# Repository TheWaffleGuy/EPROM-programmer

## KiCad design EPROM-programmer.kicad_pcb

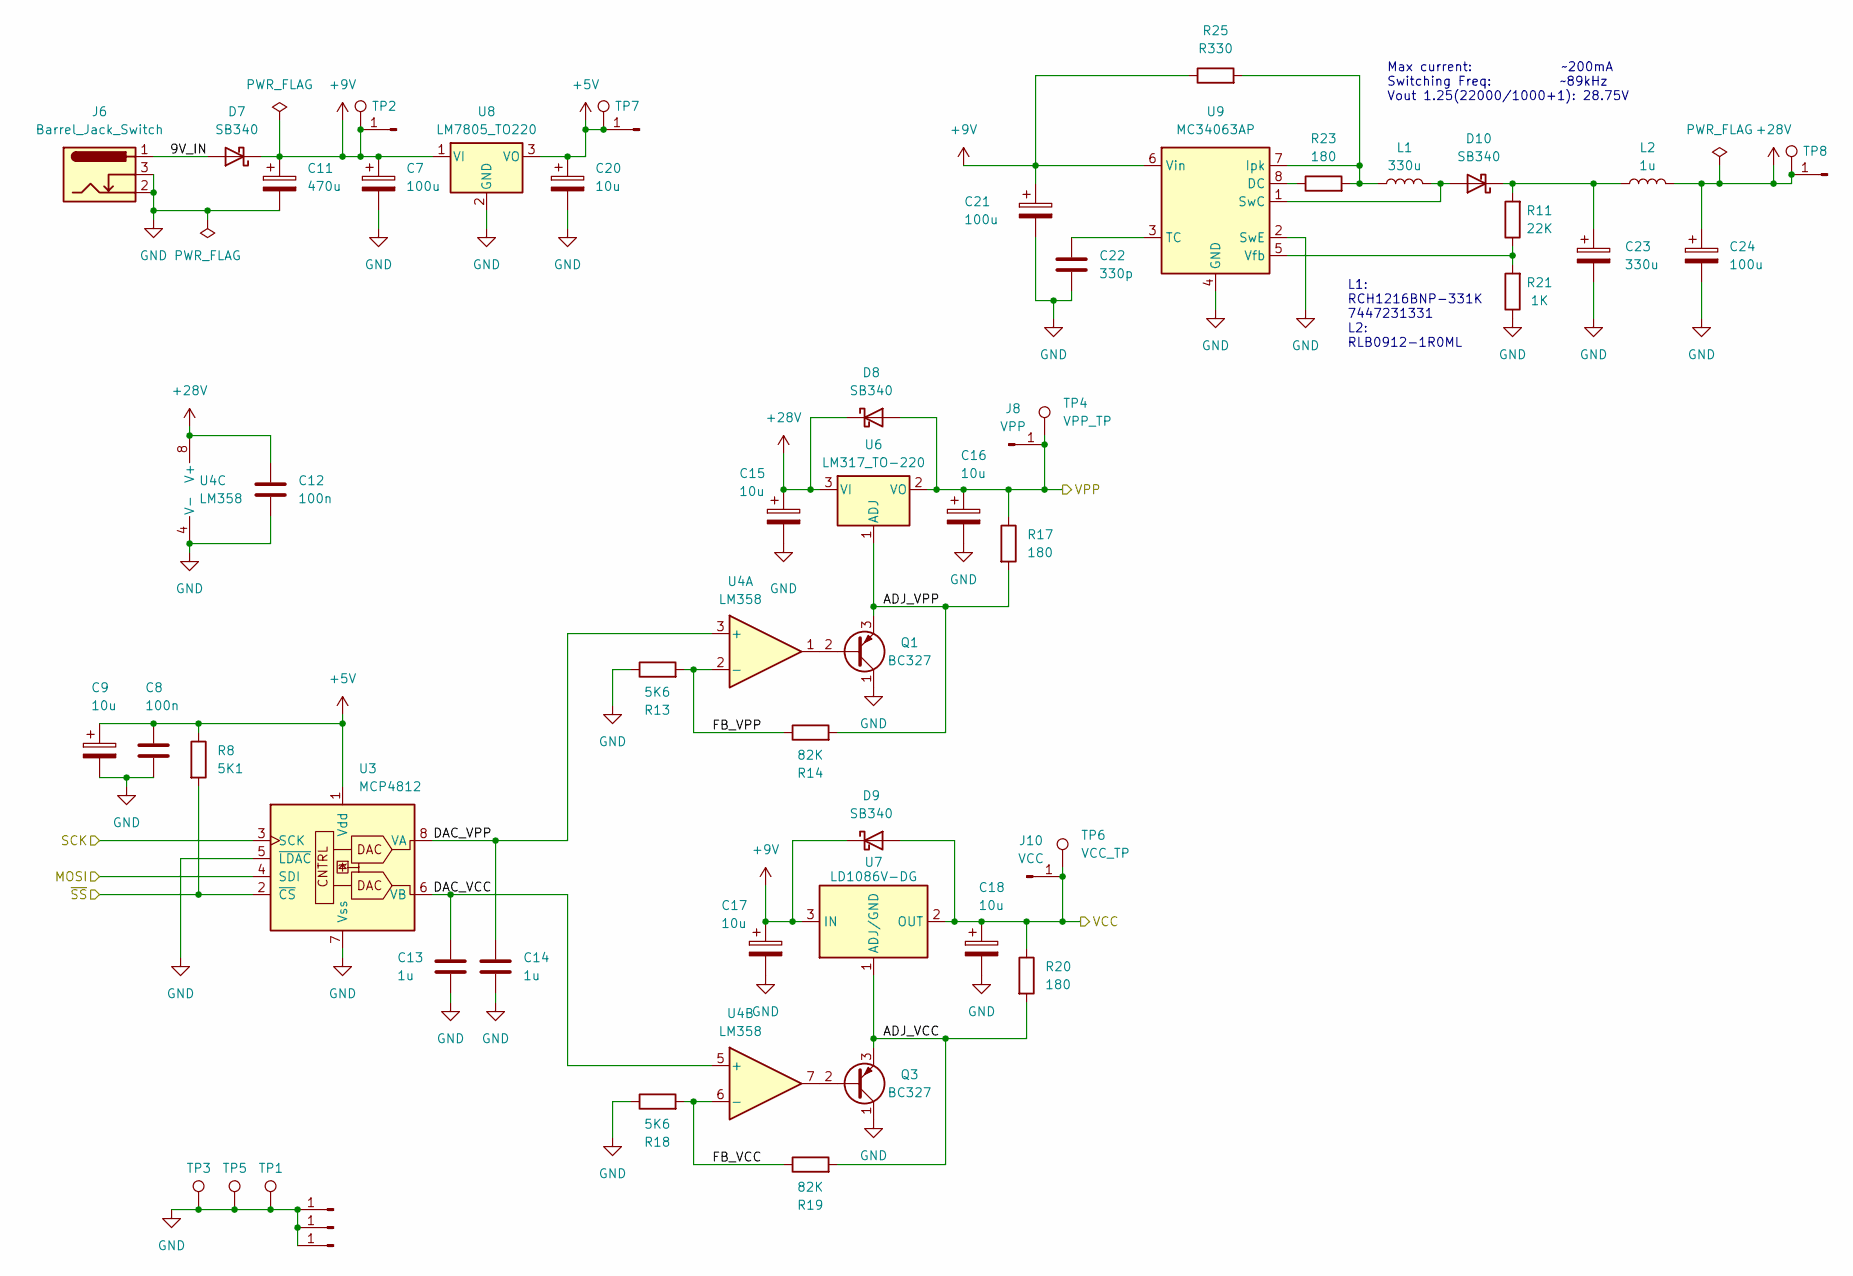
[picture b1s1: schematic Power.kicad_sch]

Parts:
C7, C21, C24: 100u; CP_Radial_D6.3mm_P2.50mm
C8, C12: 100n; C_Rect_L4.6mm_W3.0mm_P2.50mm_MKS02_FKP02
C9, C15, C16, C17, C18: 10u; C_Rect_L4.6mm_W3.0mm_P2.50mm_MKS02_FKP02
C11: 470u; CP_Radial_D10.0mm_P5.00mm
C13, C14: 1u; C_Rect_L4.6mm_W3.0mm_P2.50mm_MKS02_FKP02
C20: 10u; CP_Radial_D6.3mm_P2.50mm
C22: 330p; C_Rect_L4.6mm_W3.0mm_P2.50mm_MKS02_FKP02
C23: 330u; CP_Radial_D10.0mm_P5.00mm
D7, D8, D9, D10: SB340; D_DO-201AD_P5.08mm_Vertical_KathodeUp
J3, J5, J9: GND; PinHeader_1x01_P2.54mm_Vertical
J4: 9V; PinHeader_1x01_P2.54mm_Vertical
J6: Barrel_Jack_Switch; BarrelJack_Horizontal
J8: VPP; PinHeader_1x01_P2.54mm_Vertical
J10: VCC; PinHeader_1x01_P2.54mm_Vertical
J11: 5V; PinHeader_1x01_P2.54mm_Vertical
J12: 28V; PinHeader_1x01_P2.54mm_Vertical
L1: 330u; L_Radial_D12.5mm_P4.00mm_5.00mm
L2: 1u; L_Radial_D8.7mm_P5.00mm_Fastron_07HCP
Q1, Q3: BC327; TO-92_Inline_Wide
R8: 5K1; R_Axial_DIN0207_L6.3mm_D2.5mm_P10.16mm_Horizontal
R11: 22K; R_Axial_DIN0207_L6.3mm_D2.5mm_P10.16mm_Horizontal
R13, R18: 5K6; R_Axial_DIN0207_L6.3mm_D2.5mm_P10.16mm_Horizontal
R14, R19: 82K; R_Axial_DIN0207_L6.3mm_D2.5mm_P10.16mm_Horizontal
R17, R20, R23: 180; R_Axial_DIN0207_L6.3mm_D2.5mm_P10.16mm_Horizontal
R21: 1K; R_Axial_DIN0207_L6.3mm_D2.5mm_P10.16mm_Horizontal
R25: R330; R_Axial_DIN0207_L6.3mm_D2.5mm_P10.16mm_Horizontal
TP1, TP3, TP5: GND; TestPoint_Pad_2.0x2.0mm
TP2: 12V; TestPoint_Pad_2.0x2.0mm
TP4: VPP_TP; TestPoint_Pad_2.0x2.0mm
TP6: VCC_TP; TestPoint_Pad_2.0x2.0mm
TP7: 5V; TestPoint_Pad_2.0x2.0mm
TP8: 28V; TestPoint_Pad_2.0x2.0mm
U3: MCP4812; DIP-8_W7.62mm_Socket
U4: LM358; DIP-8_W7.62mm_Socket
U6: LM317_TO-220; TO-220-3_Vertical
U7: LD1086V-DG; TO-220-3_Horizontal_TabDown
U8: LM7805_TO220; TO-220-3_Horizontal_TabDown
U9: MC34063AP; DIP-8_W7.62mm

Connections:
+5V: C8.1, C9.1, C20.1, J11.1, R8.1, TP7.1, U3.1 (Vdd), U8.3 (VO); also elsewhere on the board
+9V: C7.1, C11.1, C17.1, C21.1, D7.1 (K), D9.1 (K), J4.1, R25.1, TP2.1, U7.3 (IN), U8.1 (VI), U9.6 (Vin)
+28V: C12.1, C15.1, C24.1, D8.1 (K), J12.1, L2.2, TP8.1, U4.8 (V+), U6.3 (VI)
/Power/9V_IN: D7.2 (A), J6.1
/Power/ADJ_VCC: Q3.3 (E), R19.2, R20.2, U7.1 (ADJ/GND)
/Power/ADJ_VPP: Q1.3 (E), R14.2, R17.2, U6.1 (ADJ)
/Power/DAC_VCC: C13.1, U3.6 (VB), U4.5 (+)
/Power/DAC_VPP: C14.1, U3.8 (VA), U4.3 (+)
/Power/FB_VCC: R18.2, R19.1, U4.6 (-)
/Power/FB_VPP: R13.2, R14.1, U4.2 (-)
/Power/VCC: C18.1, D9.2 (A), J10.1, R20.1, TP6.1, U7.2 (OUT); also elsewhere on the board
/Power/VPP: C16.1, D8.2 (A), J8.1, R17.1, TP4.1, U6.2 (VO); also elsewhere on the board
/Power/~SS: R8.2, U3.2 (~CS); also elsewhere on the board
/Programmer/MOSI: U3.4 (SDI); also elsewhere on the board
/Programmer/SCK: U3.3 (SCK); also elsewhere on the board
GND: C7.2, C8.2, C9.2, C11.2, C12.2, C13.2, C14.2, C15.2, C16.2, C17.2, C18.2, C20.2, C21.2, C22.2, C23.2, C24.2, J3.1, J5.1, J6.2, J6.3, J9.1, Q1.1 (C), Q3.1 (C), R13.1, R18.1, R21.1, TP1.1, TP3.1, TP5.1, U3.5 (~LDAC), U3.7 (Vss), U4.4 (V-), U8.2 (GND), U9.2 (SwE), U9.4 (GND); also elsewhere on the board
unnamed: D10.2 (A), L1.2, U9.1 (SwC)
unnamed: C23.1, D10.1 (K), L2.1, R11.2
unnamed: Q1.2 (B), U4.1
unnamed: Q3.2 (B), U4.7
unnamed: R23.1, U9.8 (DC)
unnamed: L1.1, R23.2, R25.2, U9.7 (Ipk)
unnamed: C22.1, U9.3 (TC)
unnamed: R11.1, R21.2, U9.5 (Vfb)

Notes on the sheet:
L1: RCH1216BNP-331K 7447231331 L2: RLB0912-1R0ML
Max current: ~200mA Switching Freq: ~89kHz Vout 1.25(22000/1000+1): 28.75V

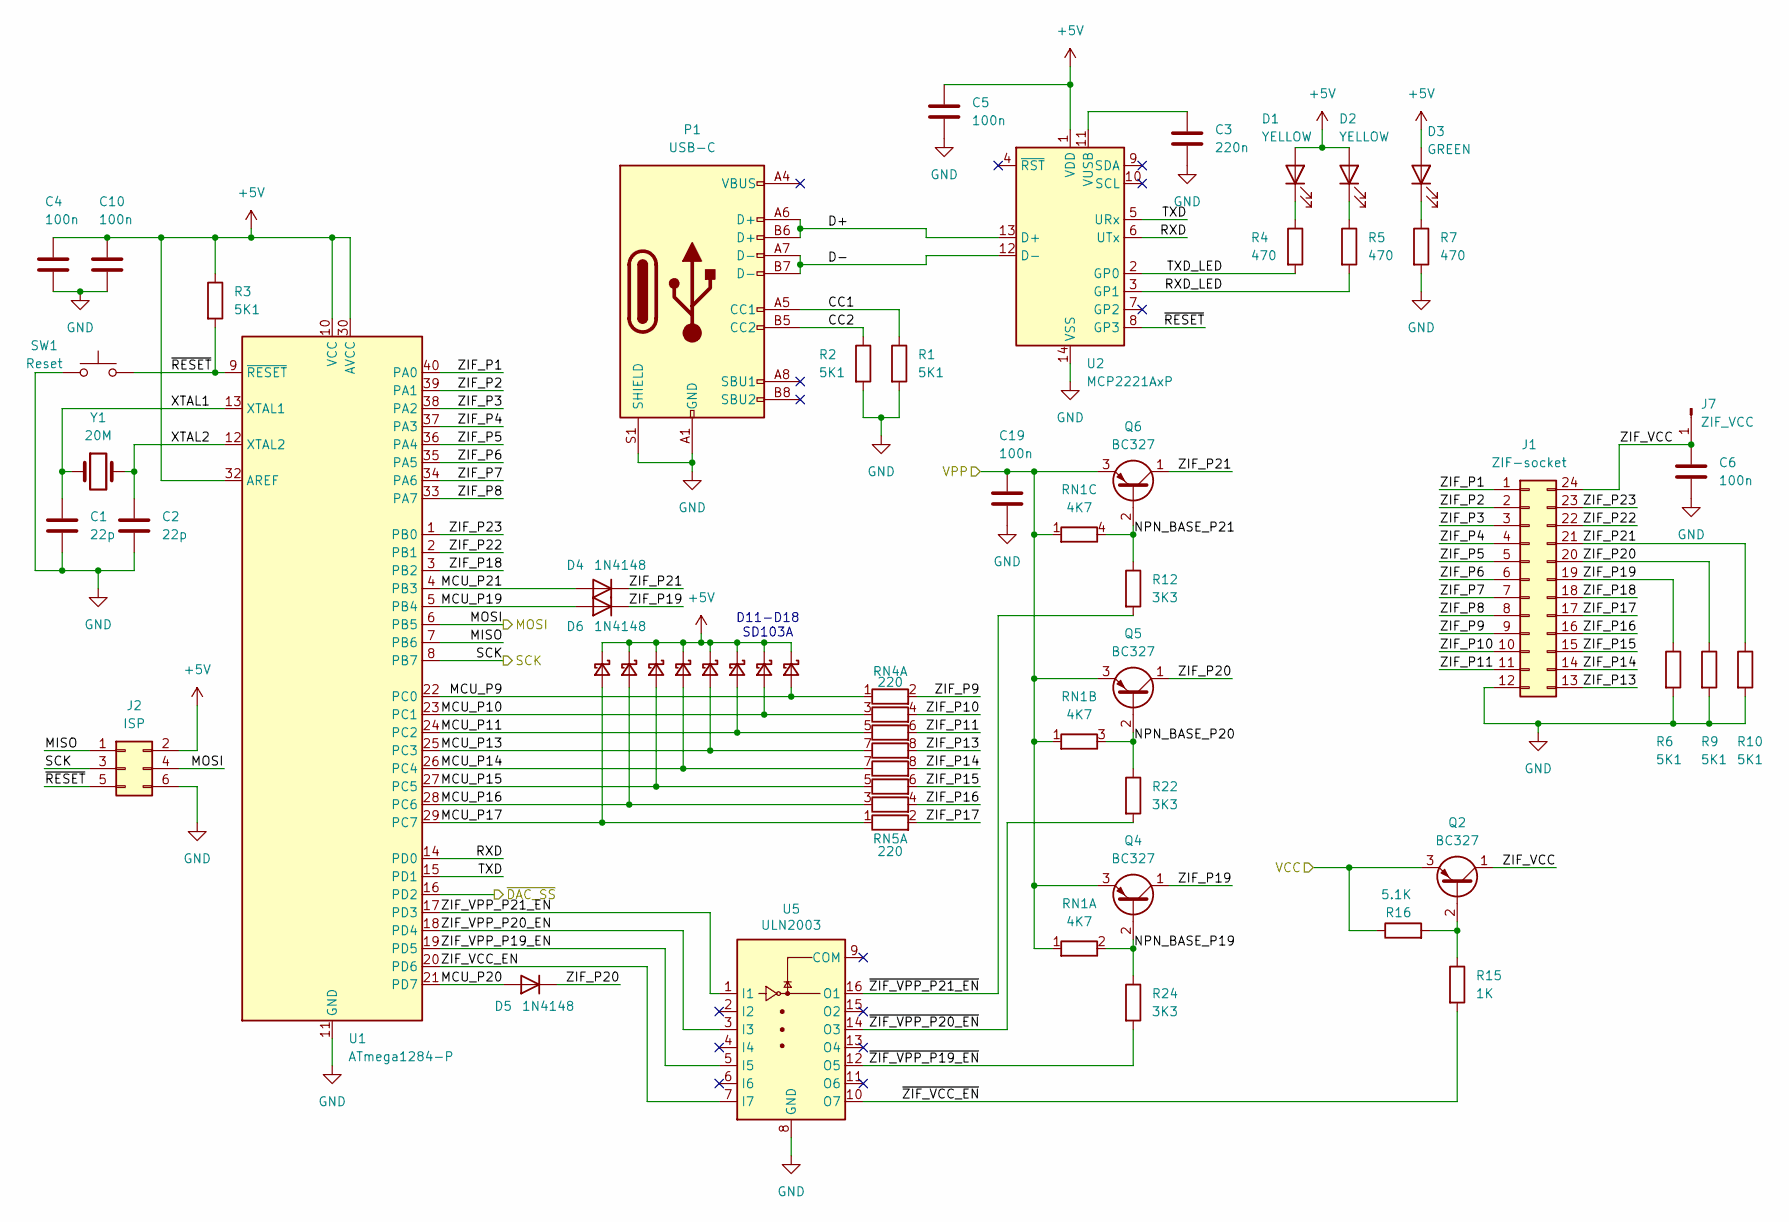
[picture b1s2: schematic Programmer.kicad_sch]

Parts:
C1, C2: 22p; C_Rect_L4.6mm_W3.0mm_P2.50mm_MKS02_FKP02
C3: 220n; C_Rect_L4.6mm_W3.0mm_P2.50mm_MKS02_FKP02
C4, C5, C6, C10, C19: 100n; C_Rect_L4.6mm_W3.0mm_P2.50mm_MKS02_FKP02
D1, D2: YELLOW; LED_D3.0mm
D3: GREEN; LED_D3.0mm
D4, D5, D6: 1N4148; D_DO-35_SOD27_P7.62mm_Horizontal
D11, D12, D13, D14, D15, D16, D17, D18: SD103A; D_DO-35_SOD27_P7.62mm_Horizontal
J1: ZIF-socket; DIP_Socket-24_W11.9_W12.7_W15.24_W17.78_W18.5_3M_224-1275-0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
J2: ISP; IDC-Header_2x03_P2.54mm_Vertical
J7: ZIF_VCC; PinHeader_1x01_P2.54mm_Vertical
P1: USB-C; USB_C_Receptacle_GCT_USB4085
Q2, Q4, Q5, Q6: BC327; TO-92_Inline_Wide
R1, R2, R3, R6, R9, R10: 5K1; R_Axial_DIN0207_L6.3mm_D2.5mm_P10.16mm_Horizontal
R4, R5, R7: 470; R_Axial_DIN0207_L6.3mm_D2.5mm_P10.16mm_Horizontal
R12, R22, R24: 3K3; R_Axial_DIN0207_L6.3mm_D2.5mm_P10.16mm_Horizontal
R15: 1K; R_Axial_DIN0207_L6.3mm_D2.5mm_P10.16mm_Horizontal
R16: 5.1K; R_Axial_DIN0207_L6.3mm_D2.5mm_P10.16mm_Horizontal
RN1: 4K7; R_Array_SIP4
RN4, RN5: 220; R_Array_SIP8
SW1: Reset; SW_PUSH_6mm
U1: ATmega1284-P; DIP-40_W15.24mm_Socket
U2: MCP2221AxP; DIP-14_W7.62mm_Socket
U5: ULN2003; DIP-16_W7.62mm
Y1: 20M; Crystal_HC49-U_Vertical

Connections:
+5V: C4.1, C5.1, C10.1, D1.2 (A), D2.2 (A), D3.2 (A), D11.1 (K), D12.1 (K), D13.1 (K), D14.1 (K), D15.1 (K), D16.1 (K), D17.1 (K), D18.1 (K), J2.2, R3.1, U1.10 (VCC), U1.30 (AVCC), U1.32 (AREF), U2.1 (VDD); also elsewhere on the board
/Power/VCC: Q2.3 (E), R16.1; also elsewhere on the board
/Power/VPP: C19.1, Q4.3 (E), Q5.3 (E), Q6.3 (E), RN1.1 (R1); also elsewhere on the board
/Power/~SS: U1.16 (PD2); also elsewhere on the board
/Programmer/CC1: P1.A5 (CC1), R1.1
/Programmer/CC2: P1.B5 (CC2), R2.1
/Programmer/D+: P1.A6 (D+), P1.B6 (D+), U2.13 (D+)
/Programmer/D-: P1.A7 (D-), P1.B7 (D-), U2.12 (D-)
/Programmer/MCU_P9: D18.2 (A), RN4.1 (R1.1), U1.22 (PC0)
/Programmer/MCU_P10: D17.2 (A), RN4.3 (R2.1), U1.23 (PC1)
/Programmer/MCU_P11: D16.2 (A), RN4.5 (R3.1), U1.24 (PC2)
/Programmer/MCU_P13: D15.2 (A), RN4.7 (R4.1), U1.25 (PC3)
/Programmer/MCU_P14: D14.2 (A), RN5.7 (R4.1), U1.26 (PC4)
/Programmer/MCU_P15: D13.2 (A), RN5.5 (R3.1), U1.27 (PC5)
/Programmer/MCU_P16: D12.2 (A), RN5.3 (R2.1), U1.28 (PC6)
/Programmer/MCU_P17: D11.2 (A), RN5.1 (R1.1), U1.29 (PC7)
/Programmer/MCU_P19: D6.2 (A), U1.5 (PB4)
/Programmer/MCU_P20: D5.2 (A), U1.21 (PD7)
/Programmer/MCU_P21: D4.2 (A), U1.4 (PB3)
/Programmer/MISO: J2.1, U1.7 (PB6)
/Programmer/MOSI: J2.4, U1.6 (PB5); also elsewhere on the board
/Programmer/NPN_BASE_P19: Q4.2 (B), R24.1, RN1.2 (R1.2)
/Programmer/NPN_BASE_P20: Q5.2 (B), R22.1, RN1.3 (R2.2)
/Programmer/NPN_BASE_P21: Q6.2 (B), R12.1, RN1.4 (R3.2)
/Programmer/RXD: U1.14 (PD0), U2.6 (UTx)
/Programmer/RXD_LED: R5.2, U2.3 (GP1)
/Programmer/SCK: J2.3, U1.8 (PB7); also elsewhere on the board
/Programmer/TXD: U1.15 (PD1), U2.5 (URx)
/Programmer/TXD_LED: R4.2, U2.2 (GP0)
/Programmer/XTAL1: C1.1, U1.13 (XTAL1), Y1.1
/Programmer/XTAL2: C2.1, U1.12 (XTAL2), Y1.2
/Programmer/ZIF_P1: J1.1, U1.40 (PA0)
/Programmer/ZIF_P2: J1.2, U1.39 (PA1)
/Programmer/ZIF_P3: J1.3, U1.38 (PA2)
/Programmer/ZIF_P4: J1.4, U1.37 (PA3)
/Programmer/ZIF_P5: J1.5, U1.36 (PA4)
/Programmer/ZIF_P6: J1.6, U1.35 (PA5)
/Programmer/ZIF_P7: J1.7, U1.34 (PA6)
/Programmer/ZIF_P8: J1.8, U1.33 (PA7)
/Programmer/ZIF_P9: J1.9, RN4.2 (R1.2)
/Programmer/ZIF_P10: J1.10, RN4.4 (R2.2)
/Programmer/ZIF_P11: J1.11, RN4.6 (R3.2)
/Programmer/ZIF_P13: J1.13, RN4.8 (R4.2)
/Programmer/ZIF_P14: J1.14, RN5.8 (R4.2)
/Programmer/ZIF_P15: J1.15, RN5.6 (R3.2)
/Programmer/ZIF_P16: J1.16, RN5.4 (R2.2)
/Programmer/ZIF_P17: J1.17, RN5.2 (R1.2)
/Programmer/ZIF_P18: J1.18, U1.3 (PB2)
/Programmer/ZIF_P19: D6.1 (K), J1.19, Q4.1 (C), R6.1
/Programmer/ZIF_P20: D5.1 (K), J1.20, Q5.1 (C), R9.1
/Programmer/ZIF_P21: D4.1 (K), J1.21, Q6.1 (C), R10.1
/Programmer/ZIF_P22: J1.22, U1.2 (PB1)
/Programmer/ZIF_P23: J1.23, U1.1 (PB0)
/Programmer/ZIF_VCC: C6.1, J1.24, J7.1, Q2.1 (C)
/Programmer/ZIF_VCC_EN: U1.20 (PD6), U5.7 (I7)
/Programmer/ZIF_VPP_P19_EN: U1.19 (PD5), U5.5 (I5)
/Programmer/ZIF_VPP_P20_EN: U1.18 (PD4), U5.3 (I3)
/Programmer/ZIF_VPP_P21_EN: U1.17 (PD3), U5.1 (I1)
/Programmer/~RESET: J2.5, R3.2, SW1.2, U1.9 (~RESET), U2.8 (GP3)
/Programmer/~ZIF_VCC_EN: R15.2, U5.10 (O7)
/Programmer/~ZIF_VPP_P19_EN: R24.2, U5.12 (O5)
/Programmer/~ZIF_VPP_P20_EN: R22.2, U5.14 (O3)
/Programmer/~ZIF_VPP_P21_EN: R12.2, U5.16 (O1)
GND: C1.2, C2.2, C3.2, C4.2, C5.2, C6.2, C10.2, C19.2, J1.12, J2.6, P1.A1 (GND), P1.A12 (GND), P1.B1 (GND), P1.B12 (GND), P1.S1 (SHIELD), R1.2, R2.2, R6.2, R7.2, R9.2, R10.2, SW1.1, U1.11 (GND), U1.31 (GND), U2.14 (VSS), U5.8 (GND); also elsewhere on the board
unnamed: D1.1 (K), R4.1
unnamed: D2.1 (K), R5.1
unnamed: D3.1 (K), R7.1
unnamed: Q2.2 (B), R15.1, R16.2
unnamed: C3.1, U2.11 (VUSB)

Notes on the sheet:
D11-D18 SD103A

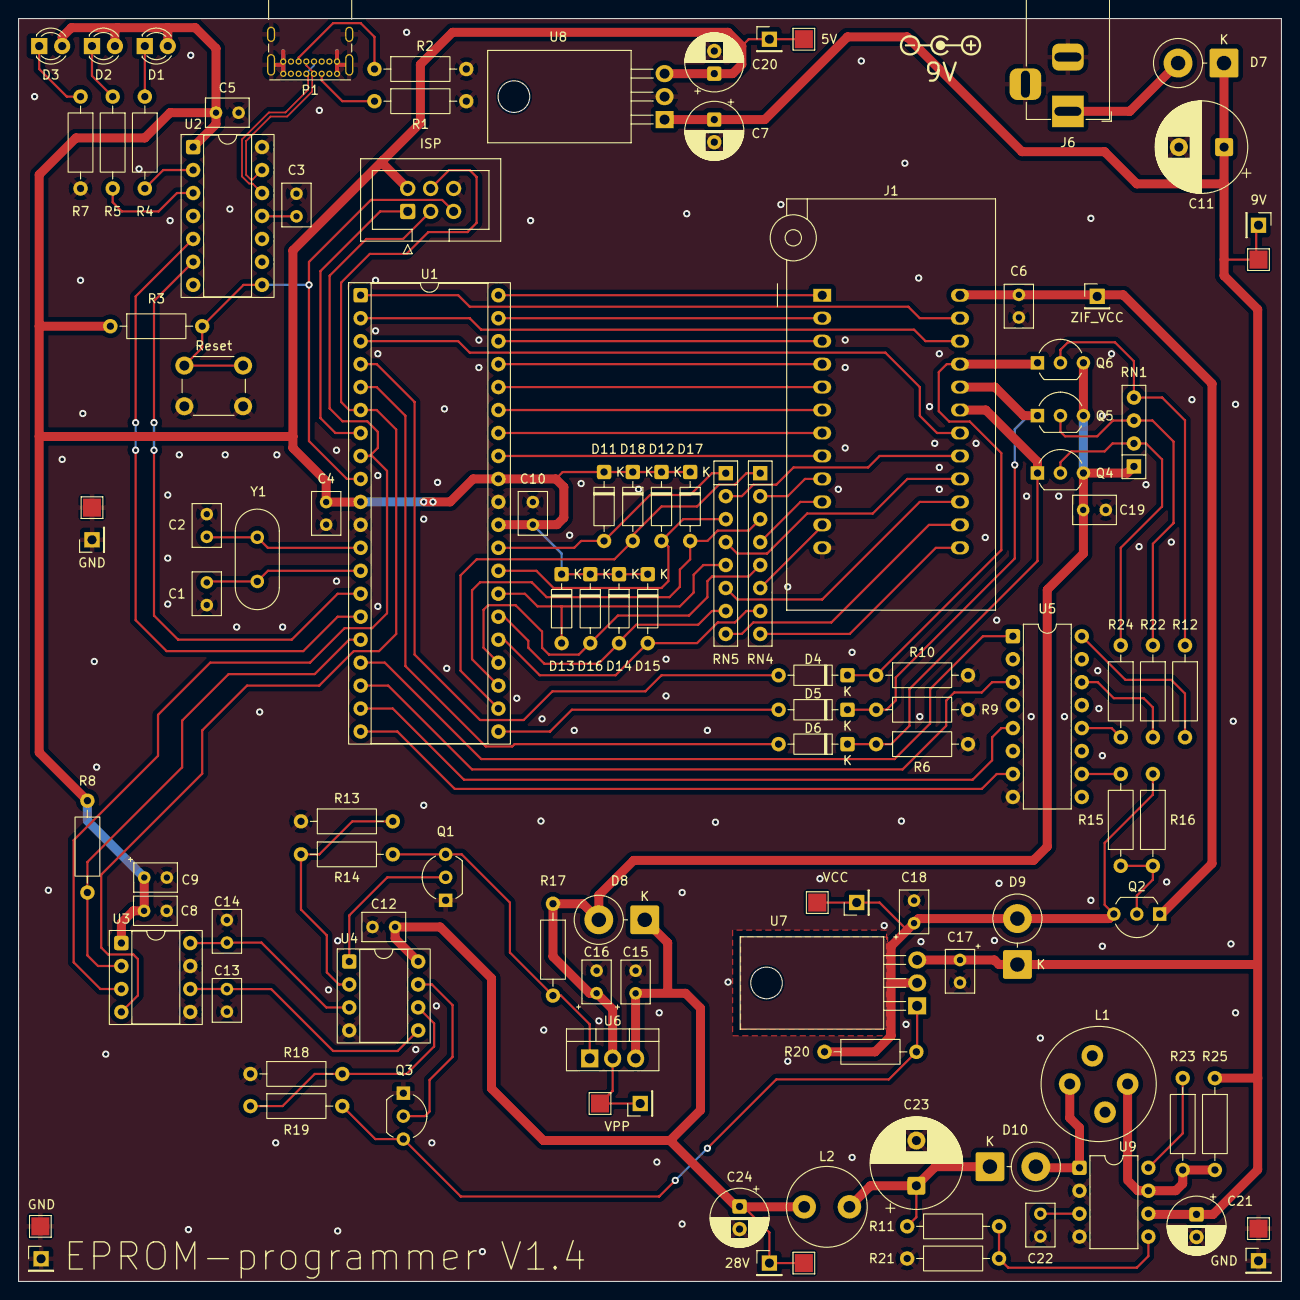
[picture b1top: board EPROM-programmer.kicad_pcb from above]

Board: 2 copper layers, 139.7 x 139.7 mm, 110 parts (0 on the bottom side), 86 nets.

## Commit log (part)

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2023-07-21 Some initial stuff
2023-07-21 Add some LEDs
2023-07-21 Add TODO
2023-07-21 Wire-up ISP, ZIF and more
2023-07-21 Add datasheets
2023-07-22 Add missing foot-prints
2023-07-22 Add power-flags
2023-07-22 Clean-up
2023-07-23 Add DAC and more
2023-07-24 Add datasheet for DAC
2023-07-24 Add some net-labels
2023-07-24 Add missing footprint
2023-07-24 Change to socket footprints
2023-07-24 Very rough component placement
2023-07-24 Add pull-up for select-line for DAC
2023-07-24 Begin routing
2023-07-24 Add more routing
2023-07-25 Update connections to ZIF-socket
2023-07-25 Add test-program
2023-07-25 Add method for writing buffer as srec
2023-07-25 Minor changes
2023-07-25 Add 57C43
2023-07-25 Update 3D-models to populated sockets
2023-07-26 Add model for ZIF-socket
2023-07-26 Minor adjustments
2023-07-26 Fix some DRC errors
2023-07-26 Initial version submitted for manufacturing
2023-07-26 Fix capacitor-stuff
2023-07-27 Begin design power
2023-07-28 Begin working on firmware
2023-07-28 Fix input/output modes of pins
2023-07-28 Send adress-data to ports
2023-07-28 Implement blank-check
2023-07-28 Fix typo
2023-07-28 Implement compare-function
2023-07-28 Print help-text when an unknown command is issued
2023-07-28 Ignore empty commands
2023-07-28 Some refactoring
2023-07-28 Refactor
2023-07-29 Add missing return statements
2023-07-29 Stupid attempt at mocking arduino
2023-07-29 Fix stupid mistake
2023-07-29 Use bit-shift instead of pow
2023-07-29 Avoid printf in print_record function
2023-07-29 Use consistent line-endings when printing serial
2023-07-29 Replace Serial.printf where trivial
2023-07-29 Add more implementations of functions for mock Serial
2023-07-29 Replace Serial.printf
2023-07-29 Remove old test-program
2023-07-29 Print name of device after device selection
2023-07-30 Fix warning
2023-07-30 Remove unused include
2023-07-30 Make commands case-insensitive
2023-07-30 Initial handling of SREC-upload
2023-07-31 Fix oops
2023-07-31 Prevent buffer overrun
2023-07-31 Fix some warnings
2023-07-31 Put device definitions in separate file
2023-07-31 Add more device definitions
2023-07-31 Prepare to handle special needs when blank-checking
2023-07-31 Add missing motorola chip
2023-07-31 Fix handling of blank-check
2023-08-06 Add manufacturer info
2023-08-11 Increase serial speed
2023-08-12 Revert "Begin design power"
    This reverts commit d1b78c65f2bc72511ae88fe321f32b0fd5b265c9.
2023-08-12 Revert "Fix capacitor-stuff"
    This reverts commit 9b25b860817774e3e25b1a31baa03ad3e26370b1.
2023-08-12 Add diodes to pins that will be used as VPP
2023-08-12 Add polarity indication to tantalum footprint
2023-08-13 Begin work on programmable VCC for ZIF
2023-08-14 Add some capacitors
2023-08-14 Add missing stuff
2023-08-15 Move stuff
2023-08-15 Add reverse polarity protection diode
2023-08-15 Do programmable VCC stuff
2023-08-15 Add new fabrication files
2023-08-23 Use union to split uint16_t and uint8_t
2023-08-23 Better handling of reading lines from serial
2023-08-24 Implement read() for Serial class
2023-08-24 Add DAC-handling
2023-08-24 Simplify DAC-handling
2023-08-26 Update arduino mock
2023-08-26 Only include arduino libs when compiling for arduino
2023-09-05 Begin development of next hardware iteration
2023-09-05 Add missing power
2023-09-05 Add missing 3D-model
2023-09-05 Prevent +5V from getting deleted during clean-up
2023-09-06 Only enable VCC when reading IC
2023-09-06 Reduce unnecessarily long delay waiting for VCC to come up
2024-02-11 Add script for reseting the MCU
2024-02-11 Ignore firmware build dir
2024-06-16 WIP use LM317
2024-06-17 Fix some ERC/DRC
2024-06-17 Fix more DRC-errors
2024-06-18 Add LM317 for VPP
2024-06-18 Very minor adjustments
2024-06-18 Update fabrication files
2024-06-18 No message
2024-06-19 Add ibom
2024-06-19 Update schematic with the missing VPP-stuff
2024-06-20 Route VPP-stuff
2024-06-20 Nudge some tracks around
2024-06-27 Add switching supply for VCC to ZIF-socket
2024-06-29 Use R-78K9.0-0.5 instead of R-78E9.0-0.5
2024-06-29 Minor adjustments to 3D-models
2024-07-06 Update voltage calculation after change to LM317
2024-07-08 Add python requirements file
2024-07-08 Add function for setting VPP
2024-07-08 Set VPP as low as possible on reset
2024-07-13 Fix mock_arduino
2024-07-14 Minor adjustments to mock hack
2024-07-14 Remove usage of String-class
2024-07-21 Fix echo of characters sent by serial
2024-07-28 Fix device turn on and turn off
2024-07-29 Store device definitions in PROGMEM
2024-07-29 Switch to more common capacitor footprint for 220uf cap
2024-07-29 Make room for heatsinks
2024-07-29 Generate new gerber-files
2024-07-29 Remove 3D model for USB-port. It's been added to builtin 3D library
2024-07-29 Prepare for using 2 layers instead of 4
2024-07-29 Move version-number to front of PCB
2024-07-29 Increase PCB size. Rework PCB to use 2 layers
2024-07-29 More silkscreen adjustments
2024-07-29 Remove some testpoints and clean up some stuff
2024-07-29 Increase base current to VCC transistor
2024-07-29 Minor silk screen adjustments
2024-07-29 Add input/output protection on data lines (WIP)
2024-07-29 Adjust component values
2024-07-29 Clean up of schematic
2024-07-29 Add aditional filter for 28v line
2024-07-29 Regenerate gerber-files
2024-07-29 Add info about polarity and voltage to PCB
2024-07-29 Finish input/output protection on data lines
2024-08-07 Change base resistors for VPP transistors
2024-08-07 Update ibom
2024-08-09 Update to handle moving of pins in new PCB revision
2024-08-09 Fix MCP2221 configuration
2024-08-28 Update handling of mock-stuff
2024-09-26 Start implementing calibration routine
2024-09-30 Fix? VCC calibration
2024-09-30 Fix calibration
2024-09-30 Remove unused variables
2024-10-02 Make global variable static and local to function
2024-10-03 Use more descriptive variable name
2024-10-03 Change help-command from ? to H
2024-10-03 Add info about voltage calibration to help-menu
2024-10-04 Add functions to turn vpp on and off
2024-10-04 Update device definitions
2024-10-05 Add VPP voltage to definitions
2024-10-05 Fix VPP voltage Signetics 27hc641
2024-10-06 Add a bunch of EPROM datasheets
2024-10-06 Add better scan
2024-10-06 Add more EPROM documentation
2024-10-06 Add Programming pulse width to device definitions
2024-10-06 Correct VPP
2024-10-06 Rename vpp_voltage -> vpp
2024-10-07 Update after using oscilloscope to look at waveforms from old programmer
2024-10-07 Found WSI algorithm datasheets
2024-10-07 Update to match datasheet
2024-10-08 Add comment about CY7C244
2024-10-08 Add more data based on measurements
2024-10-28 Add some programming parameters
2024-10-29 Add more programming parameters
2024-10-29 Add over-program pw info
2024-10-29 Remove superfluous struct member
2025-01-20 Higher quality datasheets
2025-01-22 Add better handling with multiple MCP2221 connected
2025-01-24 Fix Windows
2025-01-25 Update tool to handle programming
2025-01-26 Add error message if arduino-cli isn't found
2025-01-26 Initial work on an UI
2025-01-27 Add basic serial communication
2025-01-27 Handle backspace
2025-01-27 Start implementing some commands
2025-01-27 Add OK! message after listing devices
2025-01-27 Make sure to always print "OK!" when a command executes successfully
2025-01-27 Save calibration to EEPROM
2025-01-28 Change error-logging to Exceptions
2025-01-28 Display error message when no programmer is found
2025-01-28 Remove debug print
2025-01-29 Put voltage offsets in a struct
2025-01-29 Add some device properties
2025-01-31 Add initial work on writing an EPROM
2025-02-01 Handle 5v overprogramming
2025-02-01 Fix pw for devices with forced overprogramming
2025-02-01 Don't set the address if it's already set to the specified one
2025-02-01 Fix spelling error
2025-02-01 Add confirm prompt when burning EPROM
2025-02-01 Refactor stuff
2025-02-02 Select device by hex instead of decimal
2025-02-02 Write address padded
2025-02-02 Fix error
2025-02-02 Add workaround for long delay
2025-02-02 Burn the whole EPROM
2025-02-02 Turn of all ouputs when turning off device Add untested version of 2532 programming
2025-02-03 Add extra margin
2025-02-04 Add untested 2732 algo
2025-02-04 Add a bit of delay to help slow devices
2025-02-05 Add 2716
2025-02-06 Try to workaround some issues with slower devices
2025-02-07 Add untested cypress algo
2025-02-07 Apply VPP before programming loop where applicable
2025-02-07 Fix function name
2025-02-07 Fix comment
2025-02-07 Refactor VPP-pin handling
2025-02-09 Handle overprogram after main programming loop
2025-02-09 When overprogram is after main loop, do not set VCC in a loop
2025-02-19 Prevent window resizing to a to small size
2025-02-20 Add definition for AM2716B
2025-02-24 Add definition for AM2732B
2025-02-25 Add NMC27C16B
2025-02-25 Add NMC27C32B
2025-02-25 Fix names
2025-02-26 Correct number of pulses WS57C43C
2025-02-27 Update comment
2025-02-28 Implement TMS27C292
2025-02-28 Start preparing for refactor
2025-03-01 Refactor out devic related operations to separate file
2025-03-02 Add NMC27CxxH devices
2025-03-07 Add TMS2732A
2025-03-07 Read calibration before initializing device operations
2025-03-07 Increase program VCC slightly for signetics 27hc641
2025-03-09 Only latch new adress when needed
2025-03-09 Prevent bug when enabling 2364 mode if it is already enabled
2025-03-09 Fix verify cypress during programming
2025-03-09 Add support for "2364 mode" to CY7C264
2025-03-11 Increase delay between adress and read to handle slower ICs
2025-03-14 Add optional search-param to "L"
2025-03-14 Ignore "-" in search string
2025-03-15 Add 2758
2025-03-15 Add "datasheet" for MBM27C32A
2025-03-16 Only apply 2364-mode for compatible cypress devices
2025-03-16 Add separate entries for 2716 ICs
2025-03-16 Format list_devices to be more readable
2025-03-16 Add separate entries for 2732 ICs
2025-03-16 Change name of EPROM
2025-03-16 Add NMC27C32
2025-03-16 Minor adjustments to algorithm for AT27HC641R
2025-03-29 Remove some magic values
2025-03-29 Add rudimentary upload buffer functionality
2025-03-29 Transmit in separate thread to not block UI
2025-04-02 Update comment after testing CY7C244
2025-04-05 Inital work on device select dialog
2025-04-05 Remove unnecessary line
2025-04-14 Initial handling of commands
2025-04-14 Display selected device in toolbar
2025-04-14 Display info dialog after blank check and verify
2025-04-14 Sync selected device on start up
2025-04-14 Split manufacturer and device name to different columns in device select
2025-04-15 Handle no device selected
2025-04-15 Add support for writing EPROM from GUI
2025-04-15 Handle search in device select better
2025-04-15 Implement blank check and verify checkboxes
2025-04-24 Add TMS2508
2025-04-24 Remove unnecessary parameter
2025-04-26 Update buffer grid when opening file
2025-04-26 Handle data read from device and saving buffer to disk
2025-04-26 Do not join txThread if no such thread was created yet
2025-05-10 Fix unhandled exception when programmer is not connected
2025-07-05 Play around with urboot
2025-08-19 Start working on hw revision 1.4
2025-08-19 Fixes after KiCad 9 upgrade
2025-08-19 Redo layout after switching to LD1086
2025-08-19 Change a capacitor to a more common size
2025-08-20 Rearrange data overvoltage protection diodes
2025-08-20 Remove unnecessary external 3D models
2025-09-06 Minor adjustments primarily around data diodes
2025-09-10 Minor adjustments around VCC regulator
2025-09-11 gerbers
2026-01-23 Remove copying of data when listing devices with a filter string
2026-01-23 Fix display of device list in GUI
2026-01-25 Fix centering of error messages when starting serial
2026-01-25 Fix, UI, lines received from serial sometimes didn't split correctly
2026-01-25 Fix error when device list in UI was closed before complete list was retrieved
2026-02-14 Update device list
2026-02-18 Print some details when listing device info
2026-02-18 Add rudimentary progress bar
2026-02-20 Update progress correctly if blank check is disabled
2026-02-20 Add ability to specify voltage margin when verify/blank check EPROM
2026-02-21 Improve readability of help menu
2026-02-21 Clean up parse_margin_arg
2026-03-03 Add another Soviet EPROM
2026-03-04 Add EF2516 EPROM
